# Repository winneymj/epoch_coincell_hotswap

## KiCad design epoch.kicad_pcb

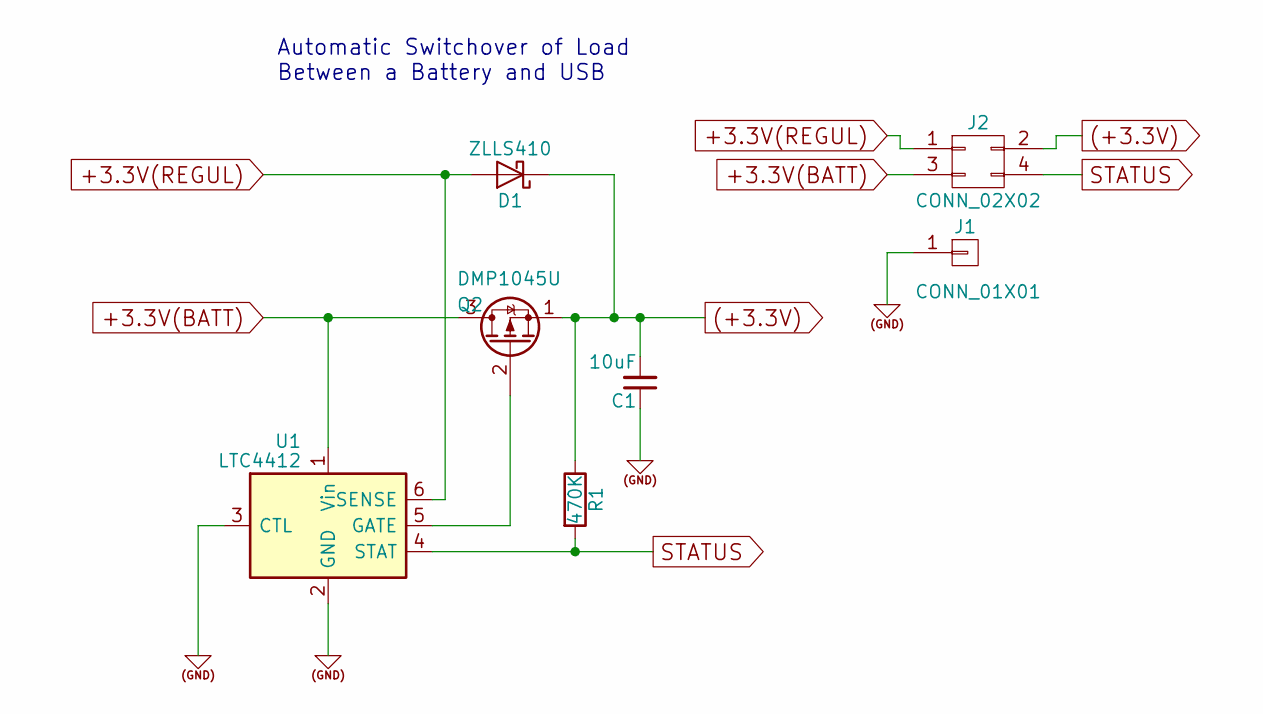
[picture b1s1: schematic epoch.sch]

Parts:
C1: 10uF; C_0805_HandSoldering
D1: ZLLS410; D_SOD-323_HandSoldering
J1: CONN_01X01; Pin_Header_Straight_1x01_Pitch1.27mm
J2: CONN_02X02; Pin_Header_Straight_2x02_Pitch1.27mm
Q2: DMP1045U; TSOT-23_HandSoldering
R1: 470K; R_0805_HandSoldering
U1: LTC4412; SOT-23-6_Handsoldering

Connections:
(+3.3V): C1.2, D1.1 (K), J2.2, Q2.1 (S), R1.1
(GND): C1.1, J1.1, U1.2 (GND), U1.3 (CTL)
+3.3V(BATT): J2.3, Q2.3 (D), U1.1 (Vin)
+3.3V(REGUL): D1.2 (A), J2.1, U1.6 (SENSE)
unnamed: Q2.2 (G), U1.5 (GATE)
STATUS: J2.4, R1.2, U1.4 (STAT)

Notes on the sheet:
Automatic Switchover of Load Between a Battery and USB

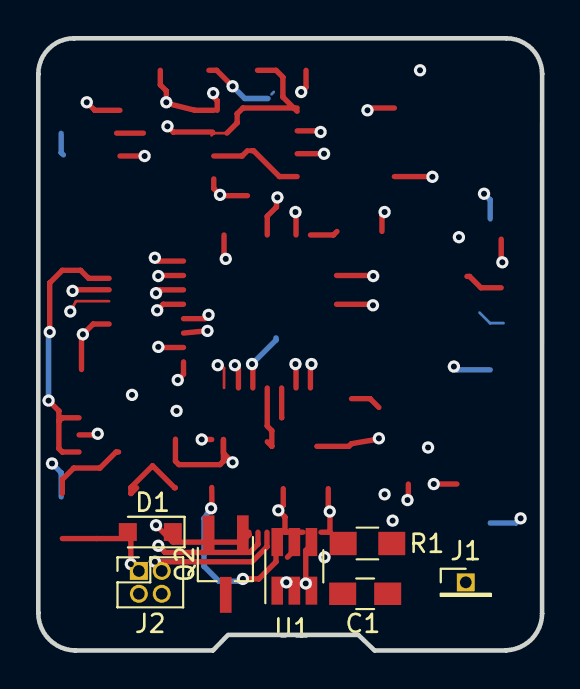
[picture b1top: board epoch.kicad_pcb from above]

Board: 2 copper layers, 28.0 x 34.0 mm, 7 parts (0 on the bottom side), 6 nets.

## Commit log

2017-09-22 Initial Version
